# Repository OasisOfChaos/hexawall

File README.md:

<!-- Improved compatibility of back to top link: See: https://github.com/othneildrew/Best-README-Template/pull/73 -->

<!-- PROJECT LOGO -->
<br />
<div align="center">

<h3 align="center">HexaWall</h3>

  <p align="center">
    <a href="https://github.com/OasisOfChaos/hexawall">GitHub page</a>
  </p>
</div>

<!-- ABOUT THE PROJECT -->
## About The Project

### A pretty big ESP32-driven LED thing for on your wall with about 60 'sequences' you can control via MQTT. 

[![Product Name Screen Shot][product-screenshot]](https://github.com/OasisOfChaos/hexawall)

The dimensions of the thing in this pic are about 1.7m by 0.7m but you can make it as large or small as you'd like.

This repo contains all the different projects to make this thing yourself:
* (PlatformIO) ESP32 firmware (this is a framework with plugin-based 'sequences')
* (Autodesk Inventor) 3D files to print the hexagons
* (Eagle) PCB files
* (Dotnet-Core 6 Blazor) website to control the thing

### Some remarks
* Every hexagon has 30 LEDS.
* I used 12VDC WS2815B ledstrips (BTF-Lighting) but because I used the FastLED library you can use a lot of other addressable strips. 
* I soldered them with separate wires but I'd advice to use the solderless connectors instead. Much easier. You may have to enlarge the hexagon a bit for this though.
* Although the PCB has a provision for powering the ESP I could not get that part to work. Maybe a timing problem or just the power supply I used (a 12V16A supply from AliExpress). In the end I just used a separate power adapter to power the ESP via USB.
* Power the LEDS from TWO sides with a wire large enough for 12VDC/8A. I used 2.5mm2 but it can probably be a bit smaller.
* Some of the sequences are made for this layout specifically. You can follow this one or just remove/rewrite the appropriate sequences.
* The hexagon 'covers' are 3mm acrylate sheets, laser cut.
* Yes, I drilled holes in my wall for the wires and control stuff.

### All this is provided as-is. I will not be able to contribute to this project in the future. Use what you like!

### A Reddit post contains some extra info: (https://www.reddit.com/r/FastLED/comments/10ue1d8/my_hexawall_project/)

<p align="right">(<a href="#readme-top">back to top</a>)</p>

<!-- MARKDOWN LINKS & IMAGES -->
<!-- https://www.markdownguide.org/basic-syntax/#reference-style-links -->
[contributors-shield]: https://img.shields.io/github/contributors/github_username/repo_name.svg?style=for-the-badge
[contributors-url]: https://github.com/github_username/repo_name/graphs/contributors
[forks-shield]: https://img.shields.io/github/forks/github_username/repo_name.svg?style=for-the-badge
[forks-url]: https://github.com/github_username/repo_name/network/members
[stars-shield]: https://img.shields.io/github/stars/github_username/repo_name.svg?style=for-the-badge
[stars-url]: https://github.com/github_username/repo_name/stargazers
[issues-shield]: https://img.shields.io/github/issues/github_username/repo_name.svg?style=for-the-badge
[issues-url]: https://github.com/github_username/repo_name/issues
[license-shield]: https://img.shields.io/github/license/github_username/repo_name.svg?style=for-the-badge
[license-url]: https://github.com/github_username/repo_name/blob/master/LICENSE.txt
[linkedin-shield]: https://img.shields.io/badge/-LinkedIn-black.svg?style=for-the-badge&logo=linkedin&colorB=555
[linkedin-url]: https://linkedin.com/in/linkedin_username
[product-screenshot]: https://github.com/OasisOfChaos/hexawall/blob/main/Images/demo.gif
[Next.js]: https://img.shields.io/badge/next.js-000000?style=for-the-badge&logo=nextdotjs&logoColor=white
[Next-url]: https://nextjs.org/
[React.js]: https://img.shields.io/badge/React-20232A?style=for-the-badge&logo=react&logoColor=61DAFB
[React-url]: https://reactjs.org/
[Vue.js]: https://img.shields.io/badge/Vue.js-35495E?style=for-the-badge&logo=vuedotjs&logoColor=4FC08D
[Vue-url]: https://vuejs.org/
[Angular.io]: https://img.shields.io/badge/Angular-DD0031?style=for-the-badge&logo=angular&logoColor=white
[Angular-url]: https://angular.io/
[Svelte.dev]: https://img.shields.io/badge/Svelte-4A4A55?style=for-the-badge&logo=svelte&logoColor=FF3E00
[Svelte-url]: https://svelte.dev/
[Laravel.com]: https://img.shields.io/badge/Laravel-FF2D20?style=for-the-badge&logo=laravel&logoColor=white
[Laravel-url]: https://laravel.com
[Bootstrap.com]: https://img.shields.io/badge/Bootstrap-563D7C?style=for-the-badge&logo=bootstrap&logoColor=white
[Bootstrap-url]: https://getbootstrap.com
[JQuery.com]: https://img.shields.io/badge/jQuery-0769AD?style=for-the-badge&logo=jquery&logoColor=white
[JQuery-url]: https://jquery.com

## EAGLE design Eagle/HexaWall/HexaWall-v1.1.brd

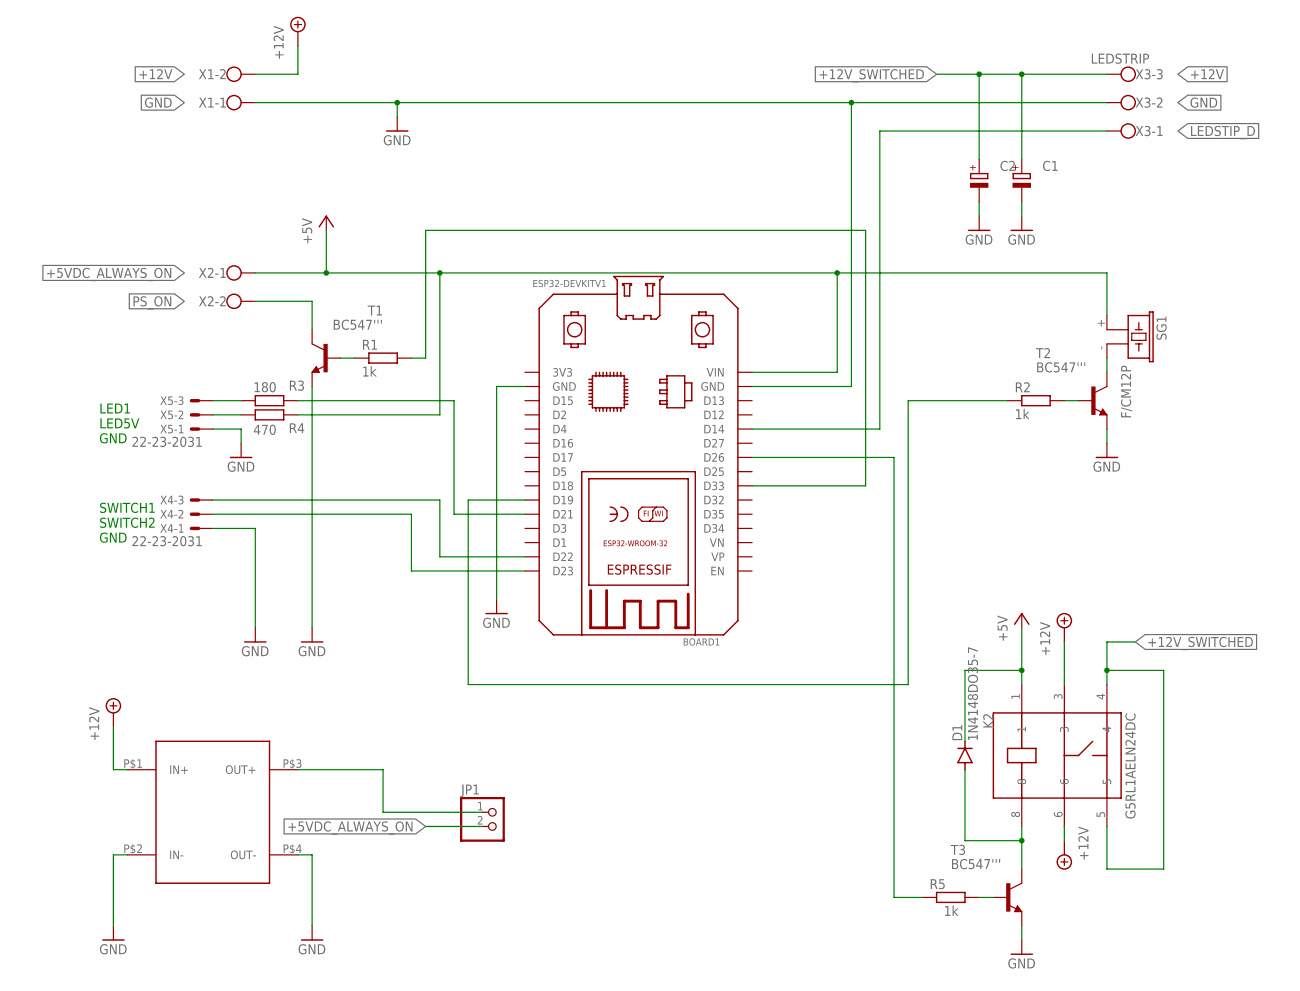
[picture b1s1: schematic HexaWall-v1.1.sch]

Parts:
BOARD1: ESP32DEVKITV1; ESP32-DEVKITV1
C1, C2: CPOL-EUE7.5-16; E7,5-16
D1: 1N4148DO35-7; DO35-7
JP1: PINHD-1X2; 1X02
K2: G5RL1AELN24DC; G5RL-1-E-HR
PS$1: DC/DC_PCB
R1, R2, R5: 1k; 0204/7
R3: 180; 0204/7
R4: 470; 0204/7
SG1: F/CM12P
T1, T2, T3: BC547'''; TO92-CBE
X1, X2: W237-102
X3: LEDSTRIP; W237-103
X4, X5: 22-23-2031

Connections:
+5VDC_ALWAYS_ON: BOARD1.VIN, D1.C, JP1.2, K2.1, R4.1, SG1.+ (1), X2.1
+12V: K2.3, K2.6, PS$1.P$1 (IN+), X1.2
+12V_SWITCHED: C1.+, C2.+, K2.4, K2.5, X3.3
GND: BOARD1.GND, C1.-, C2.-, PS$1.P$2 (IN-), PS$1.P$4 (OUT-), T1.E, T2.E, T3.E, X1.1, X3.2, X4.1, X5.1
LEDSTIP_D: BOARD1.D14, X3.1
unnamed: R5.2, T3.B
unnamed: R4.2, X5.2
unnamed: R2.2, T2.B
unnamed: BOARD1.D19, R2.1
unnamed: R1.1, T1.B
unnamed: BOARD1.D33, R1.2
unnamed: R3.2, X5.3
unnamed: D1.A, K2.8, T3.C
unnamed: BOARD1.D26, R5.1
unnamed: SG1.- (2), T2.C
unnamed: JP1.1, PS$1.P$3 (OUT+)
unnamed: BOARD1.D22, X4.3
unnamed: BOARD1.D23, X4.2
unnamed: BOARD1.D21, R3.1
PS_ON: T1.C, X2.2

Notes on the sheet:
LED1 LED5V GND
SWITCH1 SWITCH2 GND

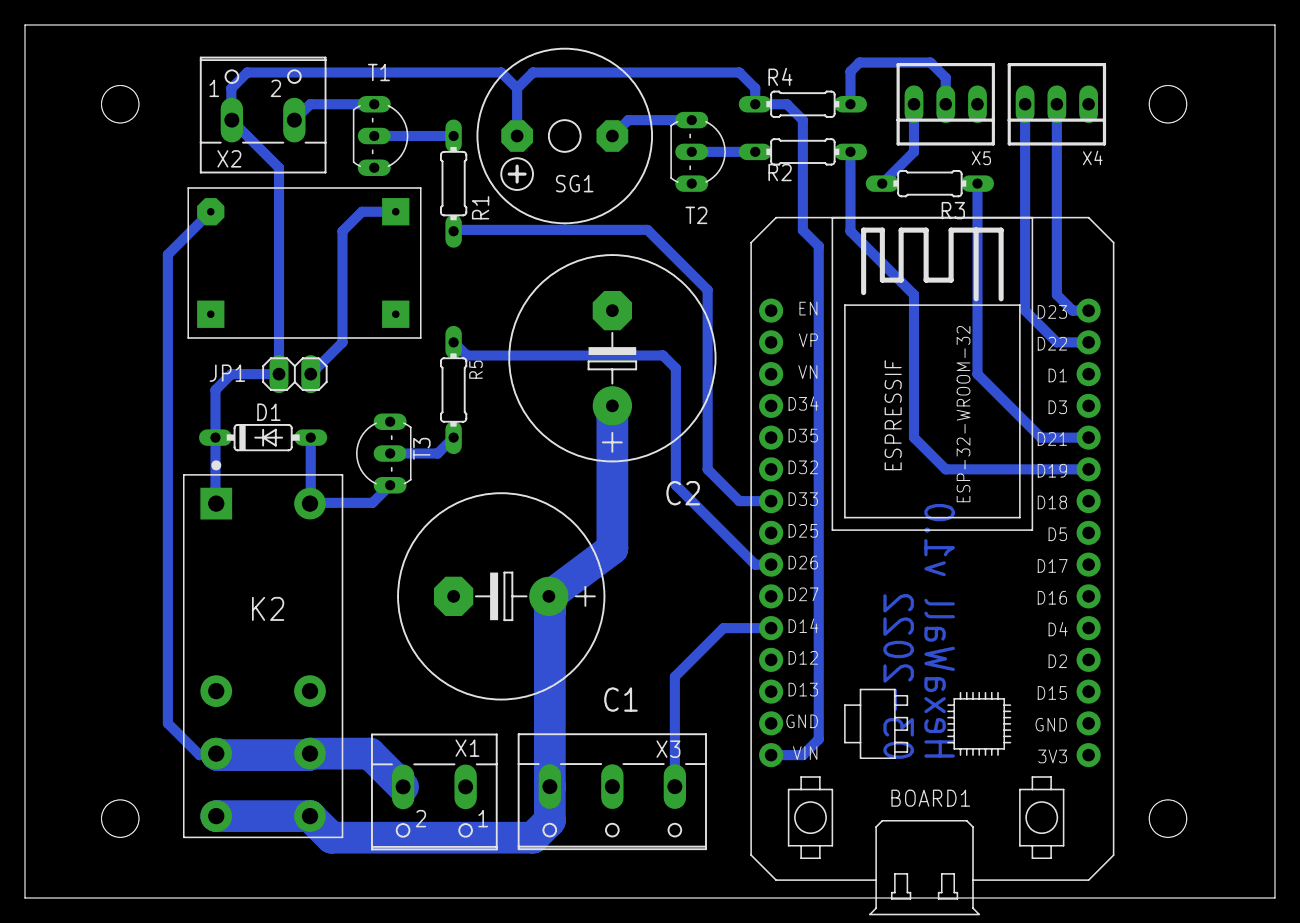
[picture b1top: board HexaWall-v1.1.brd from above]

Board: 2 copper layers, 100.0 x 69.8 mm, 22 parts (0 on the bottom side), 20 nets.

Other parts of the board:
DRILEGEND: DRILEGEND

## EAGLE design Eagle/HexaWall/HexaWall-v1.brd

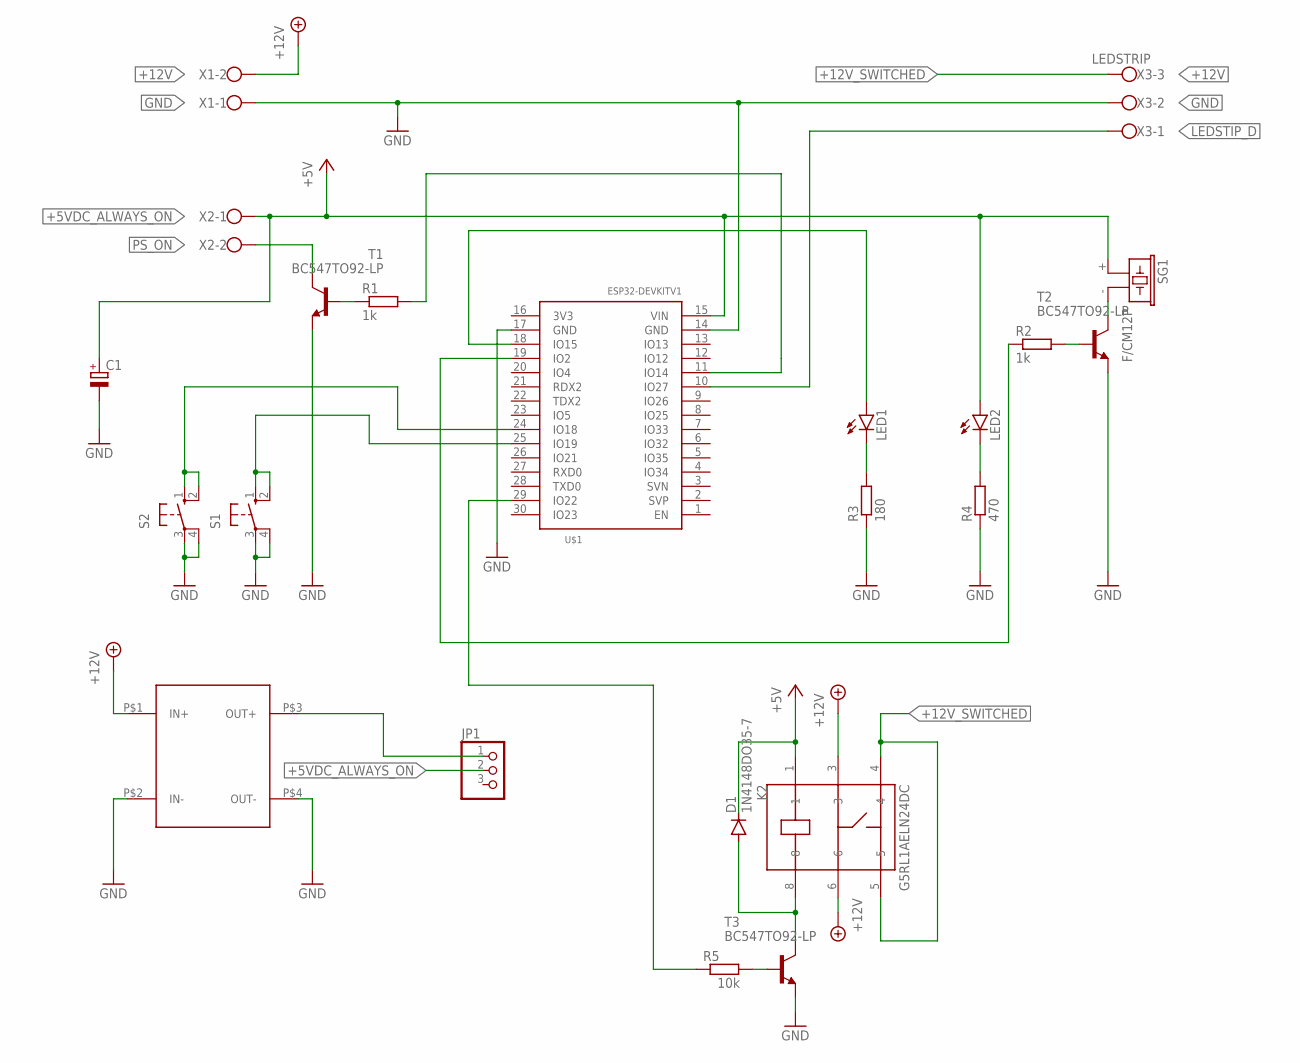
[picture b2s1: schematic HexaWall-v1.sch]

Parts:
C1: CPOL-EUE10-20; EB20D
D1: 1N4148DO35-7; DO35-7
JP1: PINHD-1X3; 1X03
K2: G5RL1AELN24DC; G5RL-1-E-HR
LED1, LED2: LED5MM
PS$1: DC/DC_PCB
R1, R2: 1k; 0204/7
R3: 180; 0204/7
R4: 470; 0204/7
R5: 10k; 0204/7
S1, S2: 40-XX; B3F-40XX
SG1: F/CM12P
T1, T2, T3: BC547TO92-LP; TO92-CBE
U$1: ESP32DEVKITV1; ESP32-DEVKITV1
X1, X2: W237-102
X3: LEDSTRIP; W237-103

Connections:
+5VDC_ALWAYS_ON: C1.+, D1.C, JP1.2, K2.1, LED2.A, SG1.+ (1), U$1.15 (VIN), X2.1
+12V: K2.3, K2.6, PS$1.P$1 (IN+), X1.2
+12V_SWITCHED: K2.4, K2.5, X3.3
GND: C1.-, PS$1.P$2 (IN-), PS$1.P$4 (OUT-), R3.1, R4.1, S1.3, S1.4 (P1), S2.3, S2.4 (P1), T1.E, T2.E, T3.E, U$1.14 (GND), U$1.17 (GND), X1.1, X3.2
LEDSTIP_D: U$1.10 (IO27), X3.1
unnamed: R5.2, T3.B
unnamed: LED1.K (C), R3.2
unnamed: R2.2, T2.B
unnamed: R2.1, U$1.19 (IO2)
unnamed: R1.1, T1.B
unnamed: R1.2, U$1.11 (IO14)
unnamed: LED2.K (C), R4.2
unnamed: D1.A, K2.8, T3.C
unnamed: R5.1, U$1.29 (IO22)
unnamed: SG1.- (2), T2.C
unnamed: LED1.A, U$1.18 (IO15)
unnamed: JP1.1, PS$1.P$3 (OUT+)
OTA_BUTTON: S2.1 (S), S2.2 (S1), U$1.24 (IO18)
POWER_BUTTON: S1.1 (S), S1.2 (S1), U$1.25 (IO19)
PS_ON: T1.C, X2.2

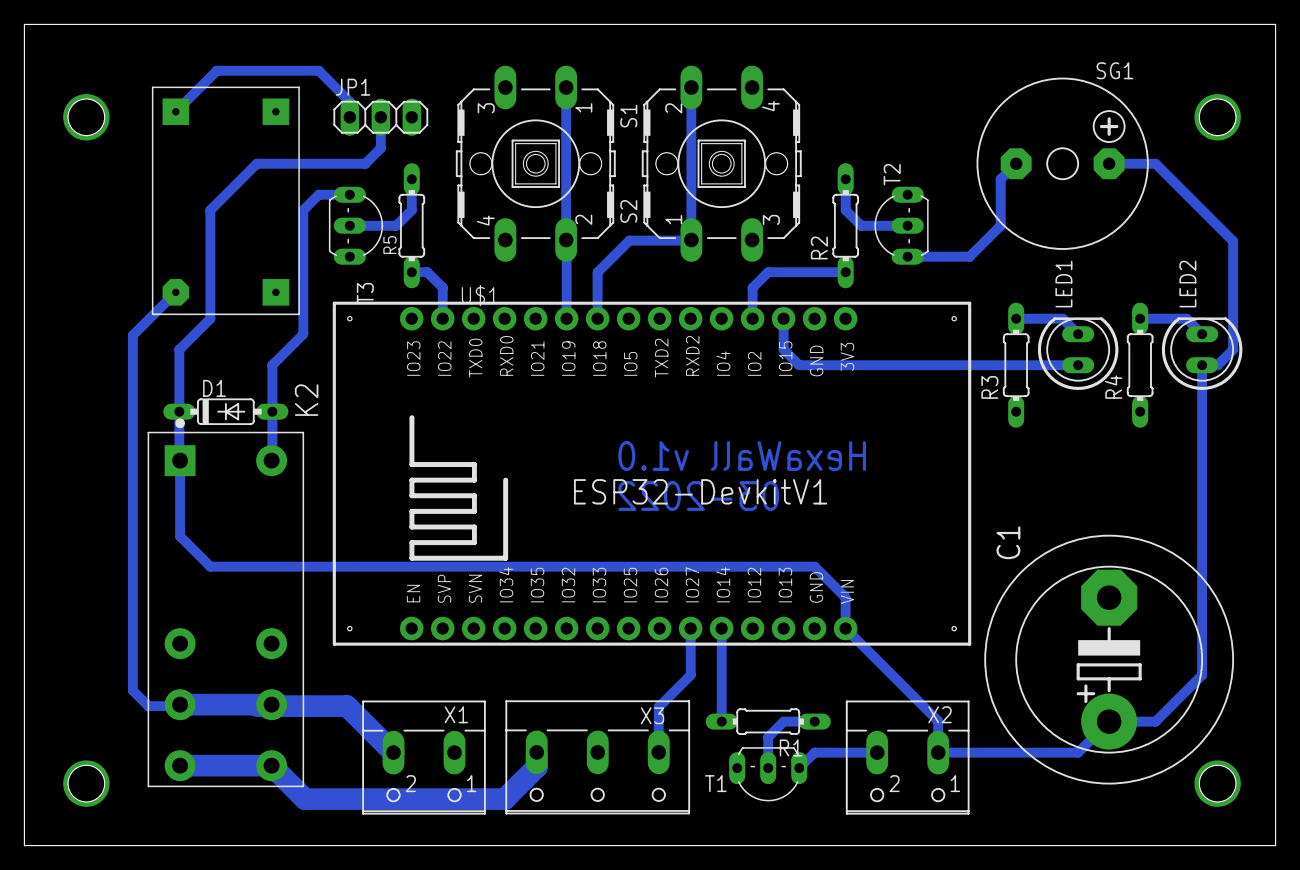
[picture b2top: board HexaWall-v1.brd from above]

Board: 2 copper layers, 102.5 x 67.3 mm, 22 parts (0 on the bottom side), 20 nets.

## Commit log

2023-02-05 initial version
2023-02-05 image location
2023-02-10 extra image
